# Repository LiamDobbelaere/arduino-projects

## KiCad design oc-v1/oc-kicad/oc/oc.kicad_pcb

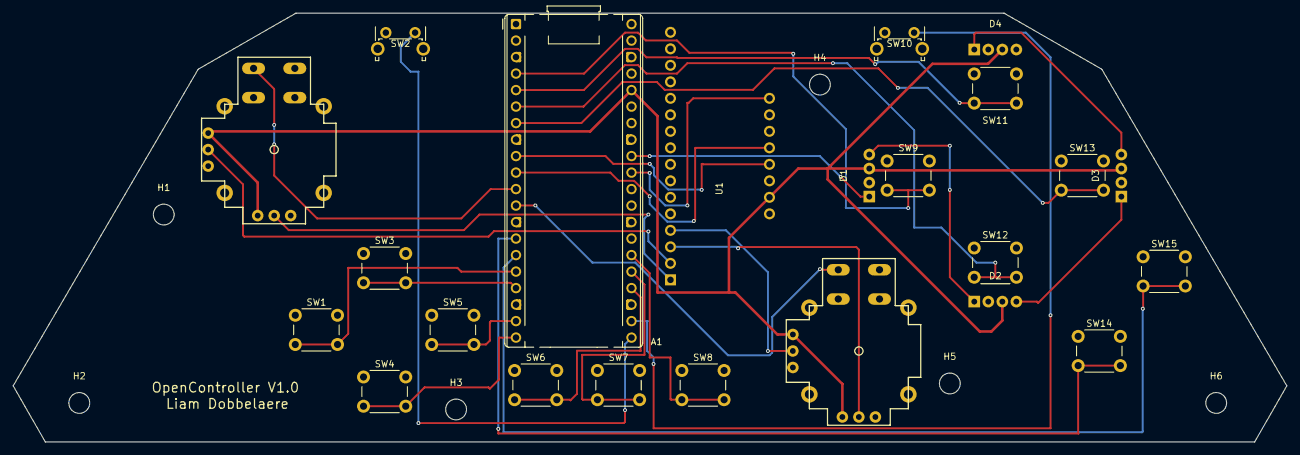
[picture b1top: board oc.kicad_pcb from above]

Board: 2 copper layers, 196.1 x 66.0 mm, 29 parts (0 on the bottom side), 30 nets.

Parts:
A1: RaspberryPi_Pico; RaspberryPi_Pico_Common_THT
D1, D2, D3, D4: LED_D5.0mm-4_RGB_Wide_Pins
H1, H2, H3, H4, H5, H6: MountingHole; MountingHole_3.2mm_M3
J1, J2: JOYSTICK
SW1, SW3, SW4, SW5, SW6, SW7, SW8, SW9, SW11, SW12, SW13, SW14, SW15: SW_Push; SW_PUSH_6mm
SW2, SW10: SW_Push; SW_Tactile_SPST_Angled_PTS645Vx58-2LFS
U1: MuxBreakout

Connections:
+3V3: A1.36 (3V3), D1.3 (VCC), D2.3 (VCC), D3.3 (VCC), D4.3 (VCC), J1.H1 (H+), J1.V1 (V+), J2.H1 (H+), J2.V1 (V+), U1.23 (VCC)
/AMUX_S0: A1.9 (GPIO6), U1.21 (S0)
/AMUX_S1: A1.10 (GPIO7), U1.20 (S1)
/AMUX_SIG: A1.31 (GPIO26_ADC0), U1.17 (SIG)
/BTN_A: A1.6 (GPIO4), SW12.2
/BTN_B: A1.7 (GPIO5), SW13.2
/BTN_C: A1.14 (GPIO10), SW14.2
/BTN_DOWN: A1.20 (GPIO15), SW4.2
/BTN_HOME: A1.25 (GPIO19), SW7.2
/BTN_LB: A1.21 (GPIO16), SW2.2
/BTN_LEFT: A1.16 (GPIO12), SW1.2
/BTN_RB: A1.22 (GPIO17), SW10.2
/BTN_RIGHT: A1.19 (GPIO14), SW5.2
/BTN_SEL: A1.24 (GPIO18), SW6.2
/BTN_START: A1.26 (GPIO20), SW8.2
/BTN_UP: A1.17 (GPIO13), SW3.2
/BTN_X: A1.4 (GPIO2), SW9.2
/BTN_Y: A1.5 (GPIO3), SW11.2
/BTN_Z: A1.15 (GPIO11), SW15.2
/JL_SEL: A1.11 (GPIO8), J1.B1A (SEL+)
/JL_X: J1.H2 (H), U1.1 (C0)
/JL_Y: J1.V2 (V), U1.2 (C1)
/JR_SEL: A1.12 (GPIO9), J2.B1A (SEL+)
/JR_X: J2.H2 (H), U1.3 (C2)
/JR_Y: J2.V2 (V), U1.4 (C3)
/RGB_DIN: A1.32 (GPIO27_ADC1), D1.1 (DIN)
GND: A1.3 (GND), A1.8 (GND), A1.13 (GND), A1.18 (GND), A1.23 (GND), A1.28 (GND), A1.33 (AGND), A1.38 (GND), D1.2 (GND), D2.2 (GND), D3.2 (GND), D4.2 (GND), J1.B2A (SEL-), J1.H3 (H-), J1.V3 (V-), J2.B2A (SEL-), J2.H3 (H-), J2.V3 (V-), SW1.1, SW2.1, SW3.1, SW4.1, SW5.1, SW6.1, SW7.1, SW8.1, SW9.1, SW10.1, SW11.1, SW12.1, SW13.1, SW14.1, SW15.1, U1.18 (S3), U1.19 (S2), U1.22 (EN), U1.24 (GND)
unnamed: D1.4 (OUTPUT), D2.1 (DIN)
unnamed: D2.4 (OUTPUT), D3.1 (DIN)
unnamed: D3.4 (OUTPUT), D4.1 (DIN)

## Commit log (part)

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2026-04-11 g2e WIP
2026-04-11 Add LED state scaffold
2026-04-12 Finish LED sequence
2026-04-12 Fix wait time
2026-04-12 Add secret
2026-04-19 Use progmem
2026-04-20 Very important change
